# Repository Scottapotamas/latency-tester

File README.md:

# Latency Tester

Small and simple board to make testing response times easier. Its basically a nice switch, phototransistor and some LEDs with IO.

Intended to be used for measuring:

- Display input latency (switch to photon time)

- Micro/Computer communications latency (switch to serial, serial to photon, etc)

- "Whole chain" timing assessments (key-switch to photon while over communications link etc)
- Human response time tests? Press the button when the light comes on...

## Electronics

- Board uses an ATSAMD M0 microcontroller. Intended for use with the Adafruit Trinket bootloader/ecosystem.

- Native USB means it can enumerate as a HID device, allowing use as a mouse/keyboard etc, or USB CDC.

- Cherry MX key-switch to act as the 'stimulus'. Photo-sensor to measure display changes as required.

- Expansion IO header provides hardware UART, along with 2 IO lines primarily intended to signal the stimulus and optical detection times. This 2x4 2.54mm header can be connected directly into a Saleae Logic analyser for timing analysis.

- 2x APA102 RGB Leds can be used to indicate state etc.
- 3mm LED in MX keyswitch is connected to the `LED_BUILTIN` pin for Arduino ecosystem, indicates bootloader state and can be used as generic user LED.
- Reset switch on bottom edge.
- SWD connector on rear isn't intended to be populated.

## Enclosure

Mostly designed to try some new modelling techniques and different enclosure approach. Intended for SLA 3D printing. I used [Lexcent](http://www.lexcent.com/).

Consists of two parts. Board slides into the halves, though some minor sanding/filing might be required depending on tolerances of SMD component placement.

I'll probably paint the 'bottom' part black, with the 'diffuse white' natural plastic allowing the top section to act as an illuminated highlight strip as depicted in the render.

## Firmware

TBD.

## Software

TBD

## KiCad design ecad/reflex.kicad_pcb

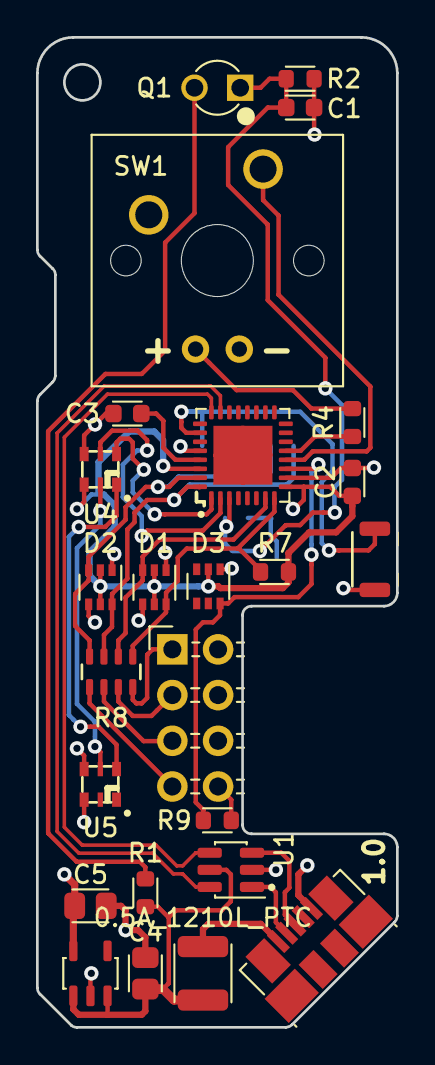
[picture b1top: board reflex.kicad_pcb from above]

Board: 2 copper layers, 20.0 x 55.0 mm, 26 parts (1 on the bottom side), 29 nets.

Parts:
C1: 1n_X7R_1608M; CAPC1608X90N
C2: 1u_X7R_1608M; CAPC1608X90N
C3: 100n_X7R_1608M; CAPC1608X90N
C4, C5: 10u_X7R_2012M; CAPC2012X110N
D1, D2, D3: BAV99_DUAL; SOT-363-6N
F1: 0.5A_1210L_PTC; FUSC3225X85L50N
J1: USB_MICRO_B_SMD_2; MOLEX_47346-0001
J2: CONN_02X04_RA; CONN_02X04_RA_MALE
Q1: BPW85C; TRANS_BCW85
R1: 0R_1608M; RESC1608X50N
R2, R7: 10K0_1608M; RESC1608X50N
R4, R9: 1K50_1608M; RESC1608X50N
R8: 100R_QUAD_ARRAY_1608M; R_Array_Concave_4x1608M
SW1: CHERRY_MX1A-E1NW_BLUE; CHERRY_MX_PCB
SW2: B3U-3000P_SPST-NO_SMD; B3U-3000P
U1: USBLC6; SOT95P280X145-6L50N
U2: ATSAMD21E18A; QFN33P50_500X500X100L40X24T345N
U3: AP2112K-3.3; SOT95P280X145-5L30N
U4, U5: APA102-2020; AP102_200X200X90L
X1: SWD_SMT_SOCKET; CNCTECH_3220-10-0300-00

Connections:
+3.3V: C2.2, C5.1, D1.2, D1.5, D2.2, D2.5, D3.2, R7.2, U2.9, U2.30, U3.5, U4.5, U5.5, X1.1
+5V: C4.1, F1.1, R1.1, U1.5, U3.1, U3.3
EXTERNAL_TRIG: D3.6, R9.2, U2.11
GND: C1.2, C2.1, C3.1, C4.2, C5.2, D1.1, D1.4, D2.1, D2.4, D3.1, J1.5, J2.6, J2.7, J2.8, R2.1, SW1.2, SW1.4, SW2.1, U1.2, U2.10, U2.28, U3.2, U4.4, U5.4, X1.3, X1.5
LED_CLK: U2.2, U4.3
LED_DATA: U2.1, U4.2
unnamed: C3.2, U2.29
unnamed: F1.2, J1.1
unnamed: J1.2, U1.1
unnamed: J1.3, U1.3
unnamed: J2.1, R8.4
unnamed: J2.2, R8.3
unnamed: J2.3, R8.2
unnamed: J2.4, R8.1
unnamed: J2.5, R9.1
unnamed: Q1.C, R1.2
unnamed: R4.1, SW1.3
unnamed: U4.1, U5.2
unnamed: U4.6, U5.3
PHOTO_TRANS: C1.1, Q1.E, R2.2, U2.3
STATUS_CAPTURE: D2.3, R8.8, U2.31, X1.4
STATUS_TRIGGER: D2.6, R8.7, U2.32, X1.2
STATUS_USER: R4.2, U2.13
SWITCH_TRIG: SW1.1, U2.12
UART_RX: D1.6, R7.1, R8.5, U2.8
UART_TX: D1.3, R8.6, U2.7
USB_D+: U1.4, U2.24
USB_D-: U1.6, U2.23
~RESET: SW2.2, U2.26, X1.10

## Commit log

2019-03-25 Adds base files for PCB
2019-03-25 Adds bulk of schematic parts
2019-03-25 Schematic changes, pcb layout
    Rough layout concepts established, started test routing
2019-03-26 Continued placement concepts and packaging ideas
2019-03-26 Routing completed
2019-03-26 Board outline cleanup, cosmetics
2019-03-26 Comments on PCB file
2019-03-28 Adds step model
2019-03-28 Adds gerber exports
2019-03-28 First pass 3D printable enclosure
    For SLA printing. Two halves
2019-03-31 Shell refinement pass
2019-03-31 Shell changes to make sure things fit
2019-04-04 Adds PCB/enclosure renders and README
2019-04-12 Fixed incorrect USB pinout to microcontroller
    Caught with prototype boards :(
2019-04-12 Super simple firmware test
    When button is down, both RGB leds cycle through the rainbow.
